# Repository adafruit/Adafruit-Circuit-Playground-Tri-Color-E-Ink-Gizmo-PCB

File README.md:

## Adafruit Circuit Playgound Tri-Color E-Ink Gizmo PCB

<a href="http://www.adafruit.com/products/4428"><br/>
Click here to purchase one from the Adafruit shop</a>

PCB files for the Adafruit Circuit Playground Tri-Color E-Ink Gizmo. 

Format is EagleCAD schematic and board layout
* https://www.adafruit.com/product/4428

### Description

Extend and expand your Circuit Playground projects with a bolt on E-Ink Gizmo that lets you add a lovely tri-color e-Ink display in a sturdy and reliable fashion. This PCB looks just like a round E-Ink breakout but has permanently affixed M3 standoffs that act as mechanical and electrical connections.

Chances are you've seen one of those new-fangled 'e-readers' like the Kindle or Nook. They have gigantic electronic paper 'static' displays - that means the image stays on the display even when power is completely disconnected. The image is also high contrast and very daylight readable. It really does look just like printed paper!

Once attached you'll get a 1.54" 152x152 display (black and red ink pixels and a white-ish background), two 3-pin STEMMA connectors for attaching NeoPixel strips or servos, and a Class D audio amplifier with a Molex PicoBlade connector that can plug one of our lil speakers.

Using our CircuitPython or Arduino library, you can create a 'frame buffer' with what pixels you want to have activated and then write that out to the display. The library we wrote does all the work for you, you can just interface with it as if it were an Adafruit_GFX compatible display. This E-Ink breakout does not contain an extra SRAM chip (not enough pins are available) so you'll need ~7K of SRAM to spare for a display buffer, the CPX has 32KB and the CPB has 256KB, so there's plenty of RAM.

This is a great companion for our Circuit Playground Express or Bluefruit boards thanks to their fast SPI hardware speeds and plenty of RAM, and works in Arduino and CircuitPython. If you're using this with Circuit Playground Express and CircuitPython, you won't be able to do a lot because there isn't a ton of memory - mostly just displaying the REPL and maybe running an image slideshow. For CircuitPython use, the Bluefruit is recommended and works really great!

You cannot use it with the Circuit Playground Classic in Arduino, there's not enough RAM!

Comes with a PCB that has pre-soldered standoffs attached, and 12x M3 screws for attachment. Fits all Circuit Playgrounds, but like we mentioned earlier, the Express and Bluefruit are recommended.

### License

Adafruit invests time and resources providing this open source design, please support Adafruit and open-source hardware by purchasing products from [Adafruit](https://www.adafruit.com)!

Designed by Limor Fried/Ladyada for Adafruit Industries.

Creative Commons Attribution/Share-Alike, all text above must be included in any redistribution. 
See license.txt for additional details.

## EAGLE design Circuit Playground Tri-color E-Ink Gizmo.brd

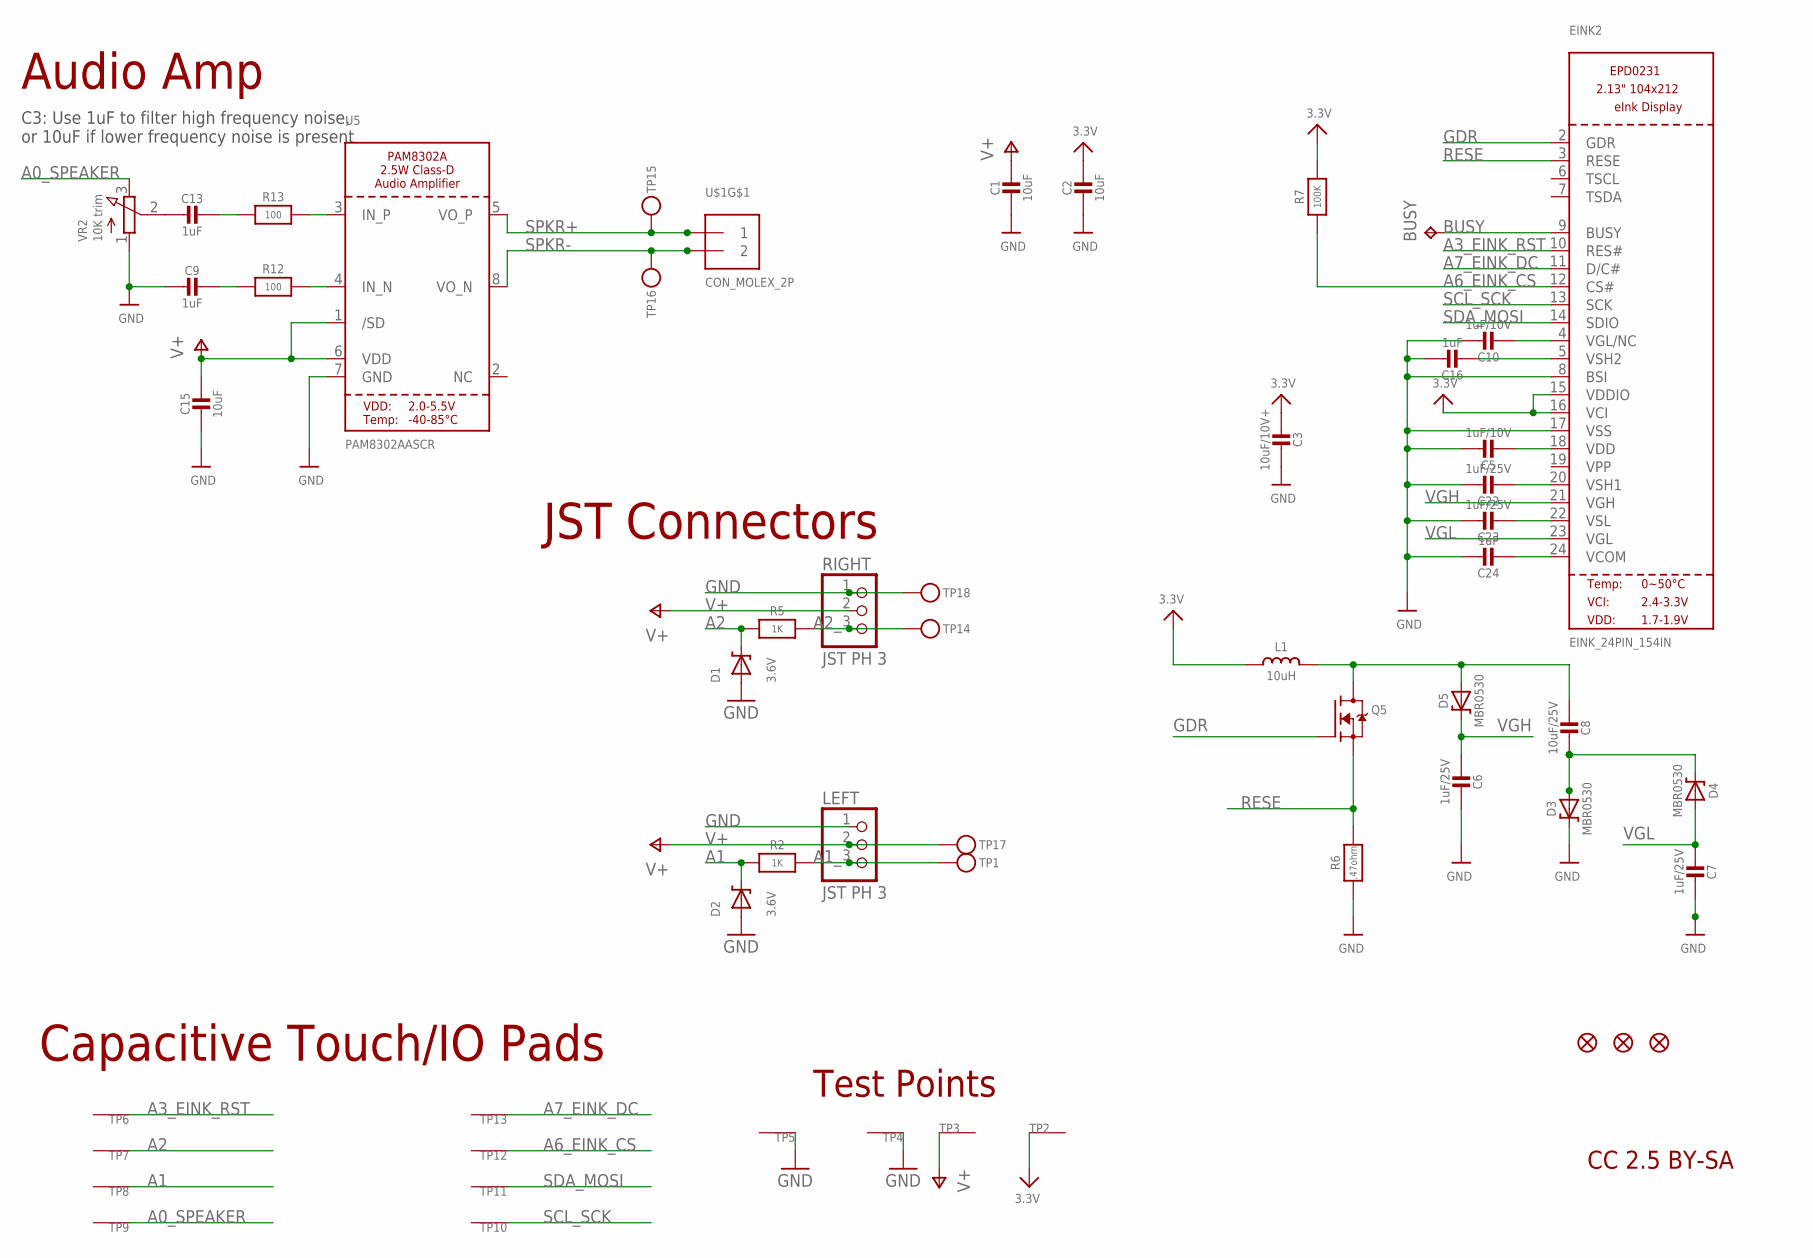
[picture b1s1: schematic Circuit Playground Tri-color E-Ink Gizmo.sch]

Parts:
BUSY: TPTP15SQ; TP15SQ
C1, C2, C15: 10uF; 0805-NO
C3: 10uF/10V+; 0805-NO
C5, C10: 1uF/10V; 0805-NO
C6, C7, C22, C23: 1uF/25V; 0805-NO
C8: 10uF/25V; 0805-NO
C9, C13, C16, C24: 1uF; 0805-NO
D1, D2: 3.6V; SOD-323
D3, D4, D5: MBR0530; SOD-123
EINK2: EINK_24PIN_154IN; EINK_154IN
L1: 10uH; INDUCTOR_4X4MM_NR401
LEFT: JST PH 3; JSTPH3
Q5: IRLML0100; SOT23-3
R2, R5: 1K; 0603-NO
R6: .47ohm; 0805_10MGAP
R7: 100K; 0603-NO
R12, R13: 100; 0603-NO
RIGHT: JST PH 3; JSTPH3
TP1, TP14, TP15, TP16, TP17, TP18: TESTPOINTROUND1.5MMNO; TESTPOINT_ROUND_1.5MM_NO
TP2, TP3, TP4, TP5, TP6, TP7, TP8, TP9, TP10, TP11, TP12, TP13: SEWTAP_SMTNUTM3; SMT_NUT_3MM
U5: PAM8302AASCR; MSOP8_0.65MM
U$1: CON_MOLEX_2P; 53398-0271
U$2, U$3, U$6: FIDUCIAL_1MM
VR2: 10K trim; TRIMPOT_BOURNS_3303W

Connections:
3.3V: C2.1, C3.2, EINK2.15 (VDDIO), EINK2.16 (VCI), L1.P$2 (2), R7.2, TP2.P$1
A0_SPEAKER: TP9.P$1, VR2.3 (E)
A1: D2.C, R2.2, TP8.P$1
A1_: LEFT.3, R2.1, TP1.P$1
A2: D1.C, R5.2, TP7.P$1
A2_: R5.1, RIGHT.3, TP14.P$1
A3_EINK_RST: EINK2.10 (RES#), TP6.P$1
A6_EINK_CS: EINK2.12 (CS#), R7.1, TP12.P$1
A7_EINK_DC: EINK2.11 (D/C#), TP13.P$1
BUSY: BUSY.TP, EINK2.9 (BUSY)
GDR: EINK2.2 (GDR), Q5.1 (G)
GND: C1.2, C2.2, C3.1, C5.1, C6.2, C7.2, C9.2, C10.1, C15.2, C16.1, C22.1, C23.1, C24.1, D1.A, D2.A, D3.C, EINK2.8 (BSI), EINK2.17 (VSS), LEFT.1, R6.2, RIGHT.1, TP4.P$1, TP5.P$1, TP18.P$1, U5.7 (GND), VR2.1 (A)
unnamed: C8.2, D3.A, D4.C
unnamed: C8.1, D5.A, L1.P$1 (1), Q5.3 (D)
unnamed: C16.2, EINK2.5 (VSH2)
unnamed: C5.2, EINK2.18 (VDD)
unnamed: C22.2, EINK2.20 (VSH1)
unnamed: C10.2, EINK2.4 (VGL/NC)
unnamed: R12.2, U5.4 (IN_N)
unnamed: R13.2, U5.3 (IN_P)
unnamed: C9.1, R12.1
unnamed: C13.1, R13.1
unnamed: C13.2, VR2.2 (S)
unnamed: C23.2, EINK2.22 (VSL)
unnamed: C24.2, EINK2.24 (VCOM)
RESE: EINK2.3 (RESE), Q5.2 (S), R6.1
SCL_SCK: EINK2.13 (SCK), TP10.P$1
SDA_MOSI: EINK2.14 (SDIO), TP11.P$1
SPKR+: TP15.P$1, U5.5 (VO_P), U$1.1
SPKR-: TP16.P$1, U5.8 (VO_N), U$1.2
V+: C1.1, C15.1, LEFT.2, RIGHT.2, TP3.P$1, TP17.P$1, U5.1 (/SD), U5.6 (VDD)
VGH: C6.1, D5.C, EINK2.21 (VGH)
VGL: C7.1, D4.A, EINK2.23 (VGL)

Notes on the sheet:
CC 2.5 BY-SA
Capacitive Touch/IO Pads
C3: Use 1uF to filter high frequency noise, or 10uF if lower frequency noise is present
Audio Amp
Test Points
JST Connectors

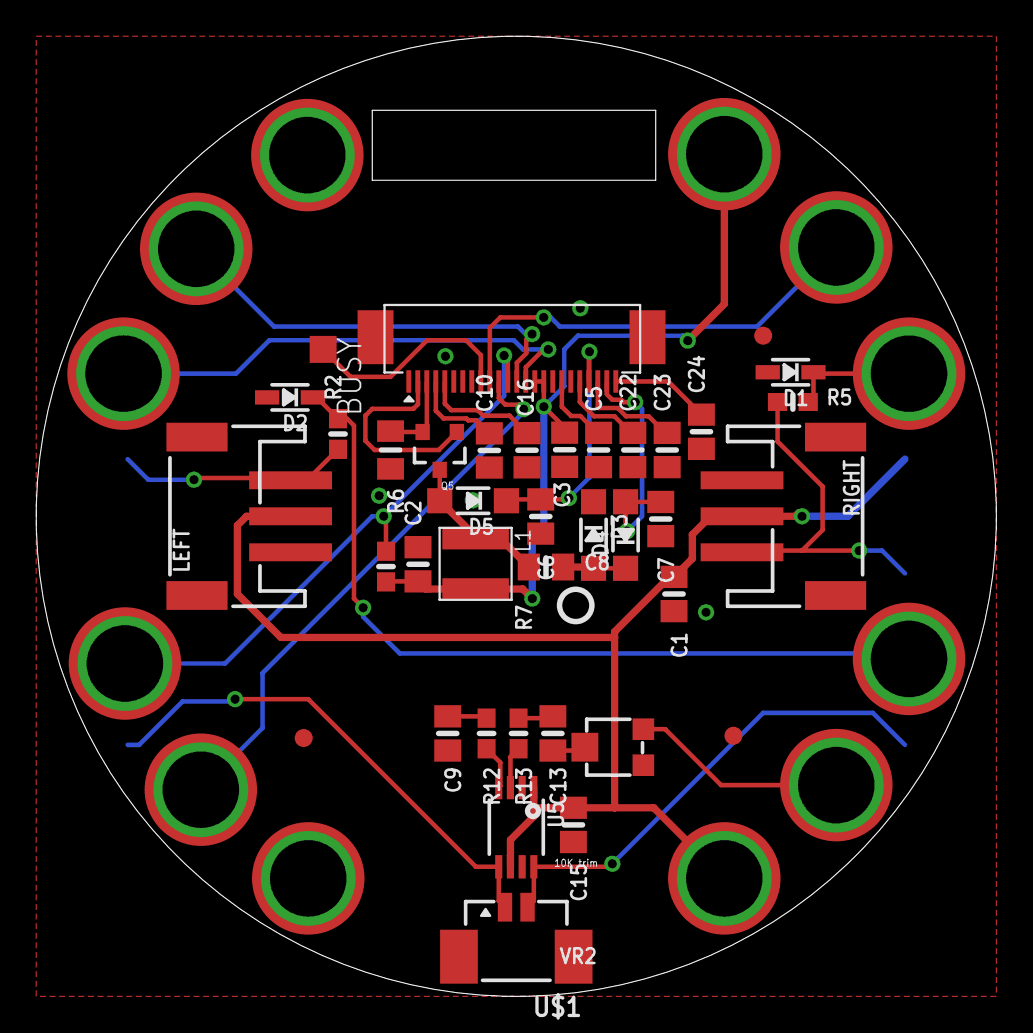
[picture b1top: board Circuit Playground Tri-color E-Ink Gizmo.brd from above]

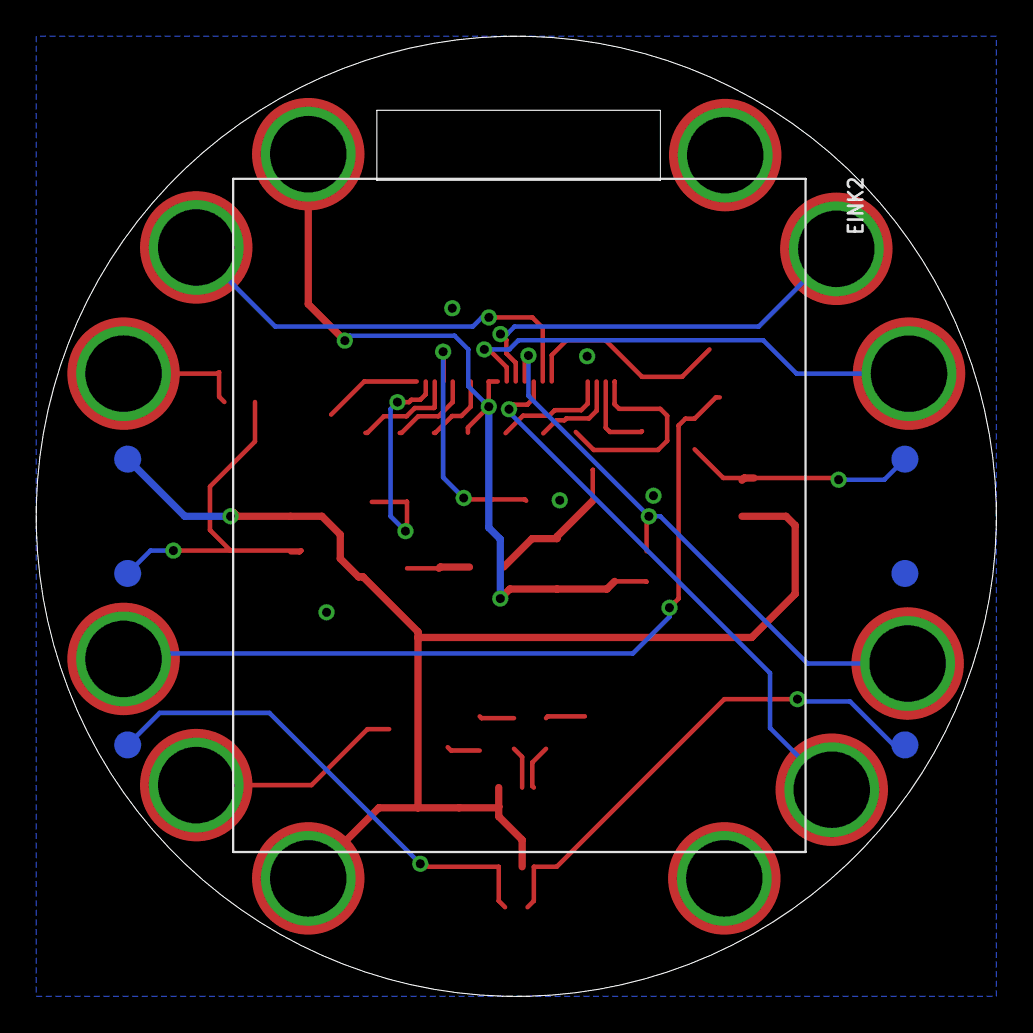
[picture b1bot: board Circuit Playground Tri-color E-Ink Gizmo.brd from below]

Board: 2 copper layers, 53.3 x 53.3 mm, 59 parts (8 on the bottom side), 33 nets.

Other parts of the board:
U$4: EINKGIZMO_BACK
U$7: PCBFEAT-REV-040
U$8: EINKGIZMO_FRONT

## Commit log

2019-11-20 Adding board files.
2020-09-07 Fixed typo

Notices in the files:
parts and their libraries:
microbuilder: This work is placed in the public domain, and may be freely used for commercial and non-commercial work with the following conditions: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
